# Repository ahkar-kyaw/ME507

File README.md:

# ME507 Fall 2025
### Team Members
- Agregado, Fred
- Kyaw, Ahkar
- Power, Alex

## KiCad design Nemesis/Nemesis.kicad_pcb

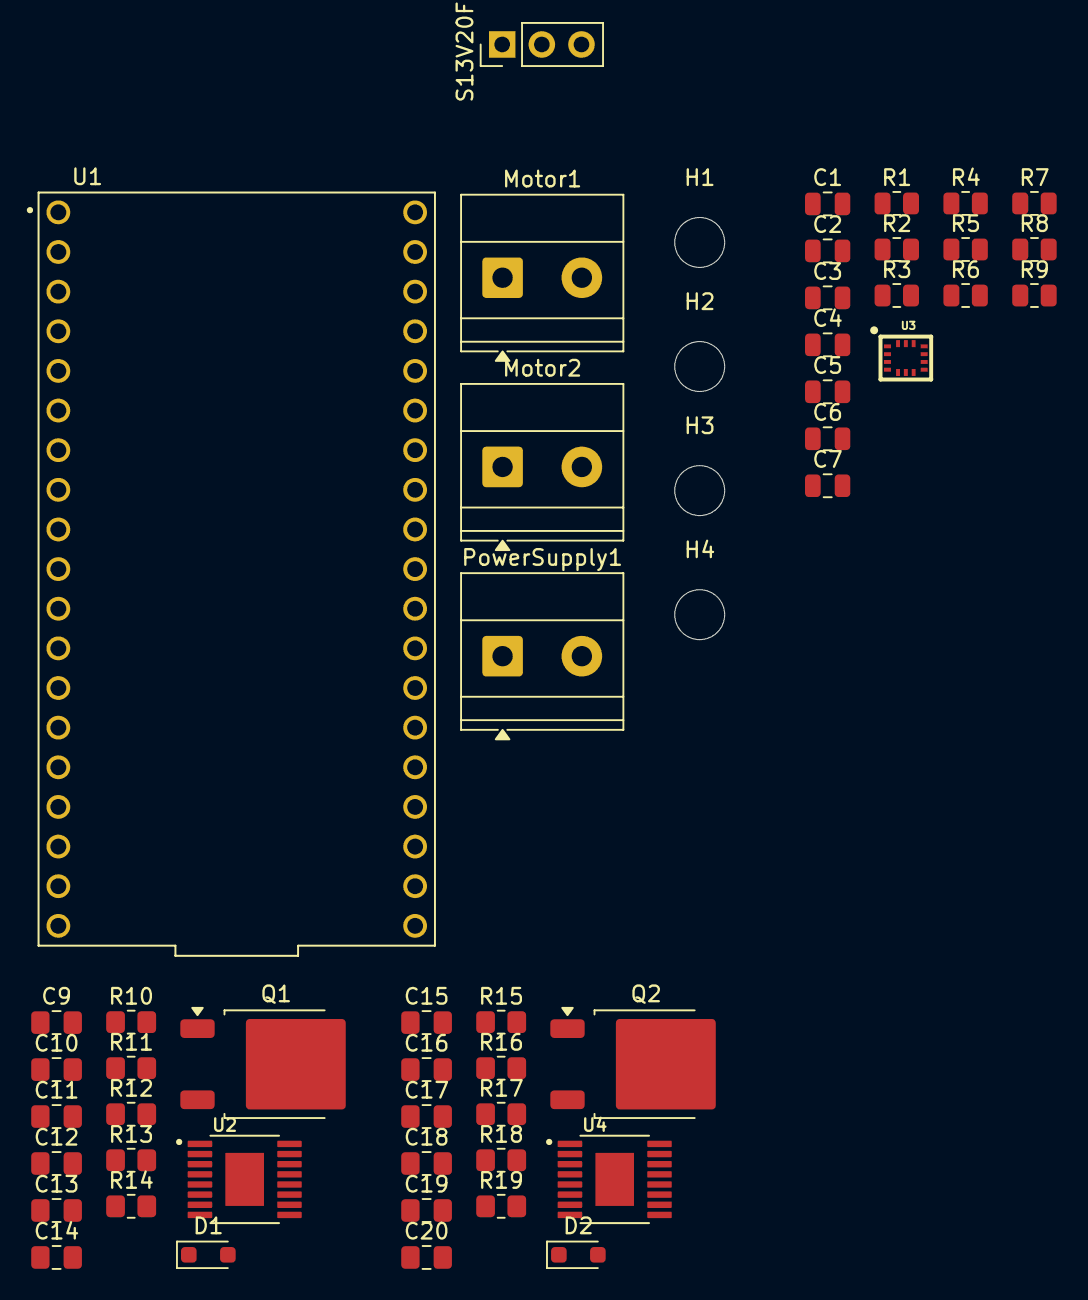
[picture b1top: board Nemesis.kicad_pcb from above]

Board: 2 copper layers, 54 parts (0 on the bottom side), 35 nets, no tracks yet.

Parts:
C1: 1.0 uF; C_0805_2012Metric
C2, C6, C7: 0.1 uF; C_0805_2012Metric
C3, C4: 4.7 uF; C_0805_2012Metric
C5: 1 uF; C_0805_2012Metric
C9, C15: 220nF; C_0805_2012Metric_Pad1.18x1.45mm_HandSolder
C10, C11, C16, C17: 4.7nF; C_0805_2012Metric_Pad1.18x1.45mm_HandSolder
C12, C13, C18, C19: 0.1nF; C_0805_2012Metric_Pad1.18x1.45mm_HandSolder
C14, C20: 22nF; C_0805_2012Metric_Pad1.18x1.45mm_HandSolder
D1, D2: 16.2V; D_SOD-323_HandSoldering
H1, H2, H3, H4: MountingHole; MountingHole_3.2mm_M3
Motor1, Motor2: Screw_Terminal_01x02; TerminalBlock_Phoenix_MKDS-1,5-2-5.08_1x02_P5.08mm_Horizont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
PowerSupply1: Screw_Terminal_01x02; TerminalBlock_Phoenix_MKDS-1,5-2-5.08_1x02_P5.08mm_Horizont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
Q1, Q2: Q_PMOS; TO-252-2
R1, R2, R3, R4, R5, R6, R7, R8, R9: 10k; R_0805_2012Metric
R10, R15: 20k; R_0805_2012Metric_Pad1.20x1.40mm_HandSolder
R11, R16: 10k; R_0805_2012Metric_Pad1.20x1.40mm_HandSolder
R12, R17: NP; R_0805_2012Metric_Pad1.20x1.40mm_HandSolder
R13, R18: 100k; R_0805_2012Metric_Pad1.20x1.40mm_HandSolder
R14, R19: 2.49k; R_0805_2012Metric_Pad1.20x1.40mm_HandSolder
S13V20F5: Voltage Regulator; PinHeader_1x03_P2.54mm_Vertical
U1: NODEMCU-32S
U2, U4: DRV8874PWPR
U3: LSM6DSO

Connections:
+3V3: C1.1, C2.1, C3.1, C4.1, C5.1, C6.1, C7.1, R1.1, R2.1, R3.2, R4.2, R5.2, R6.2, R7.2, R8.2, R9.2, R11.1, R16.1, U1.J1_1 (3.3V), U2.3 (NSLEEP), U3.5 (VDDIO), U3.8 (VDD), U4.3 (NSLEEP)
+5V: S13V20F5.1, U1.J1_19 (5V)
/DRV8874-1/CS: R14.1, U2.6 (IPROPI)
/DRV8874-1/IMODE: R10.1, U2.7 (IMODE)
/DRV8874-1/OUT1: Motor1.1, U2.8 (OUT1)
/DRV8874-1/OUT2: Motor1.2, U2.10 (OUT2)
/DRV8874-1/VM: C9.2, U2.11 (VM)
/DRV8874-1/VREF: R11.2, R12.1, U2.5 (VREF)
/DRV8874-2/CS: R19.1, U4.6 (IPROPI)
/DRV8874-2/IMODE: R15.1, U4.7 (IMODE)
/DRV8874-2/OUT1: Motor2.1, U4.8 (OUT1)
/DRV8874-2/OUT2: Motor2.2, U4.10 (OUT2)
/DRV8874-2/VM: C15.2, U4.11 (VM)
/DRV8874-2/VREF: R16.2, R17.1, U4.5 (VREF)
/GPIO14: U1.J1_12 (IO14), U4.1 (EN/IN1)
/GPIO16: U1.J2_12 (IO16), U2.2 (PH/IN2)
/GPIO17: U1.J2_11 (IO17), U2.1 (EN/IN1)
/GPIO21: R1.2, R3.1, U1.J2_6 (IO21), U3.14 (SDA)
/GPIO22: R2.2, R4.1, U1.J2_3 (IO22), U3.13 (SCL)
/GPIO27: U1.J1_11 (IO27), U4.2 (PH/IN2)
/LSM6DSO/CS: R6.1, U3.12 (~CS)
/LSM6DSO/OCS Aux: R9.1, U3.10 (OCSX)
/LSM6DSO/SCx: R8.1, U3.3 (SCX)
/LSM6DSO/SDO: R5.1, U3.1 (SDO/SA0)
/LSM6DSO/SDx: R7.1, U3.2 (SDIX)
/VMOT: C10.2, C11.2, C12.2, C13.2, C16.2, C17.2, C18.2, C19.2, D1.1 (K), D2.1 (K), PowerSupply1.1, S13V20F5.3
GND: C1.2, C2.2, C3.2, C4.2, C5.2, C6.2, C7.2, C10.1, C11.1, C12.1, C13.1, C16.1, C17.1, C18.1, C19.1, PowerSupply1.2, R10.2, R12.2, R13.2, R14.2, R15.2, R17.2, R18.2, R19.2, S13V20F5.2, U1.J1_14 (GND), U1.J2_1 (GND), U1.J2_7 (GND), U2.9 (PGND), U2.15 (GND), U2.16 (PMODE), U3.6 (GND@6), U3.7 (GND@7), U4.9 (PGND), U4.15 (GND), U4.16 (PMODE)
unnamed: D1.2 (A), R13.1
unnamed: D2.2 (A), R18.1
unnamed: C14.1, U2.13 (CPH)
unnamed: C14.2, U2.14 (CPL)
unnamed: C9.1, U2.12 (VCP)
unnamed: C20.1, U4.13 (CPH)
unnamed: C20.2, U4.14 (CPL)
unnamed: C15.1, U4.12 (VCP)

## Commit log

2025-10-17 Fix formatting of Team Members section
